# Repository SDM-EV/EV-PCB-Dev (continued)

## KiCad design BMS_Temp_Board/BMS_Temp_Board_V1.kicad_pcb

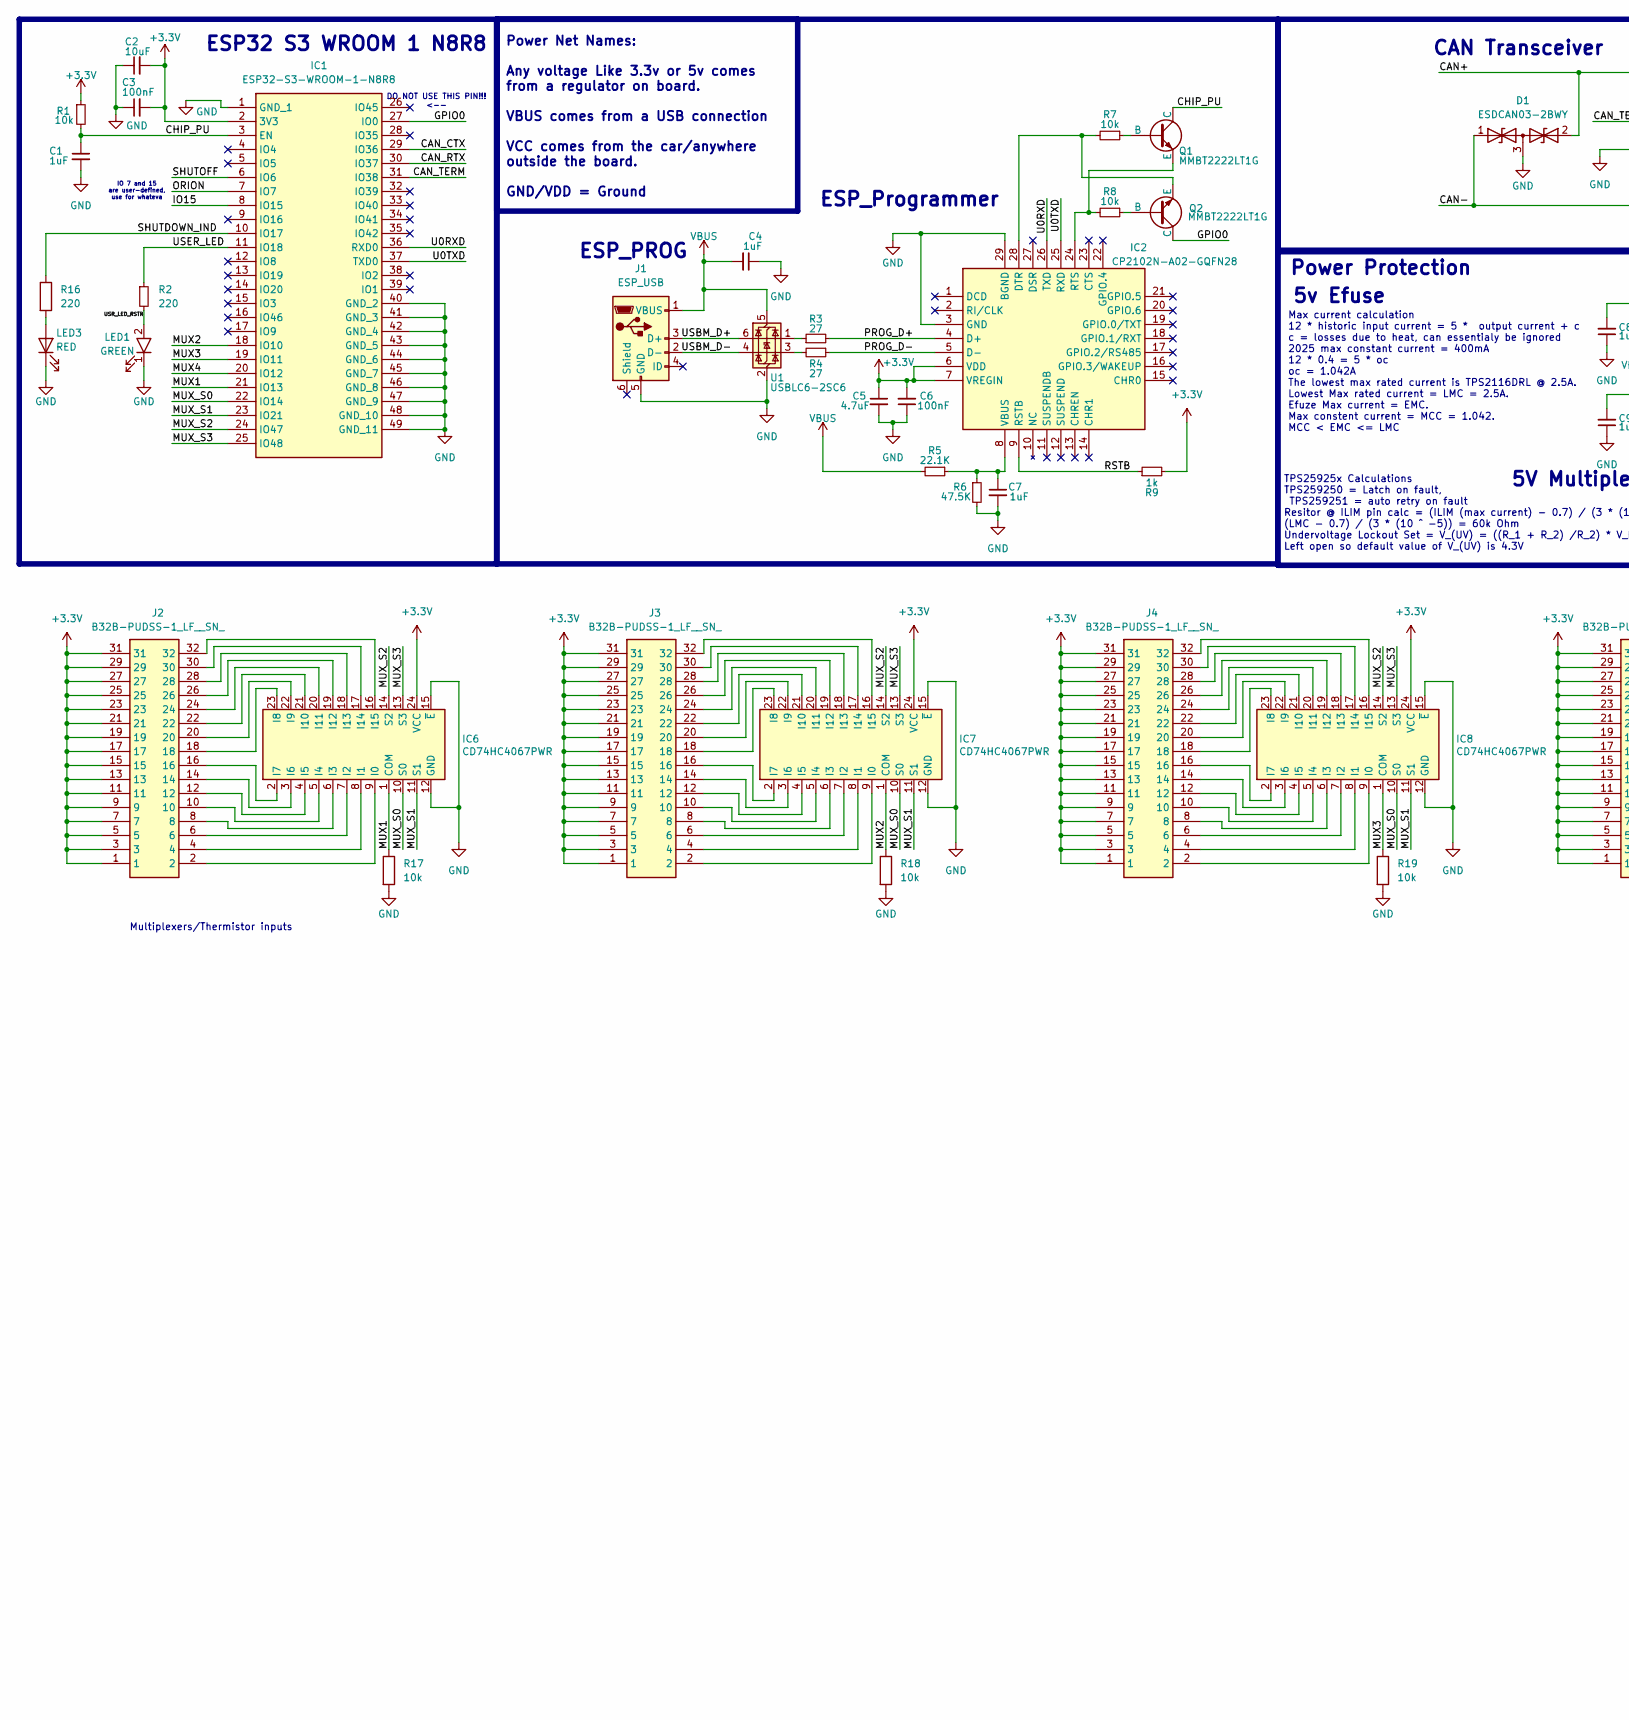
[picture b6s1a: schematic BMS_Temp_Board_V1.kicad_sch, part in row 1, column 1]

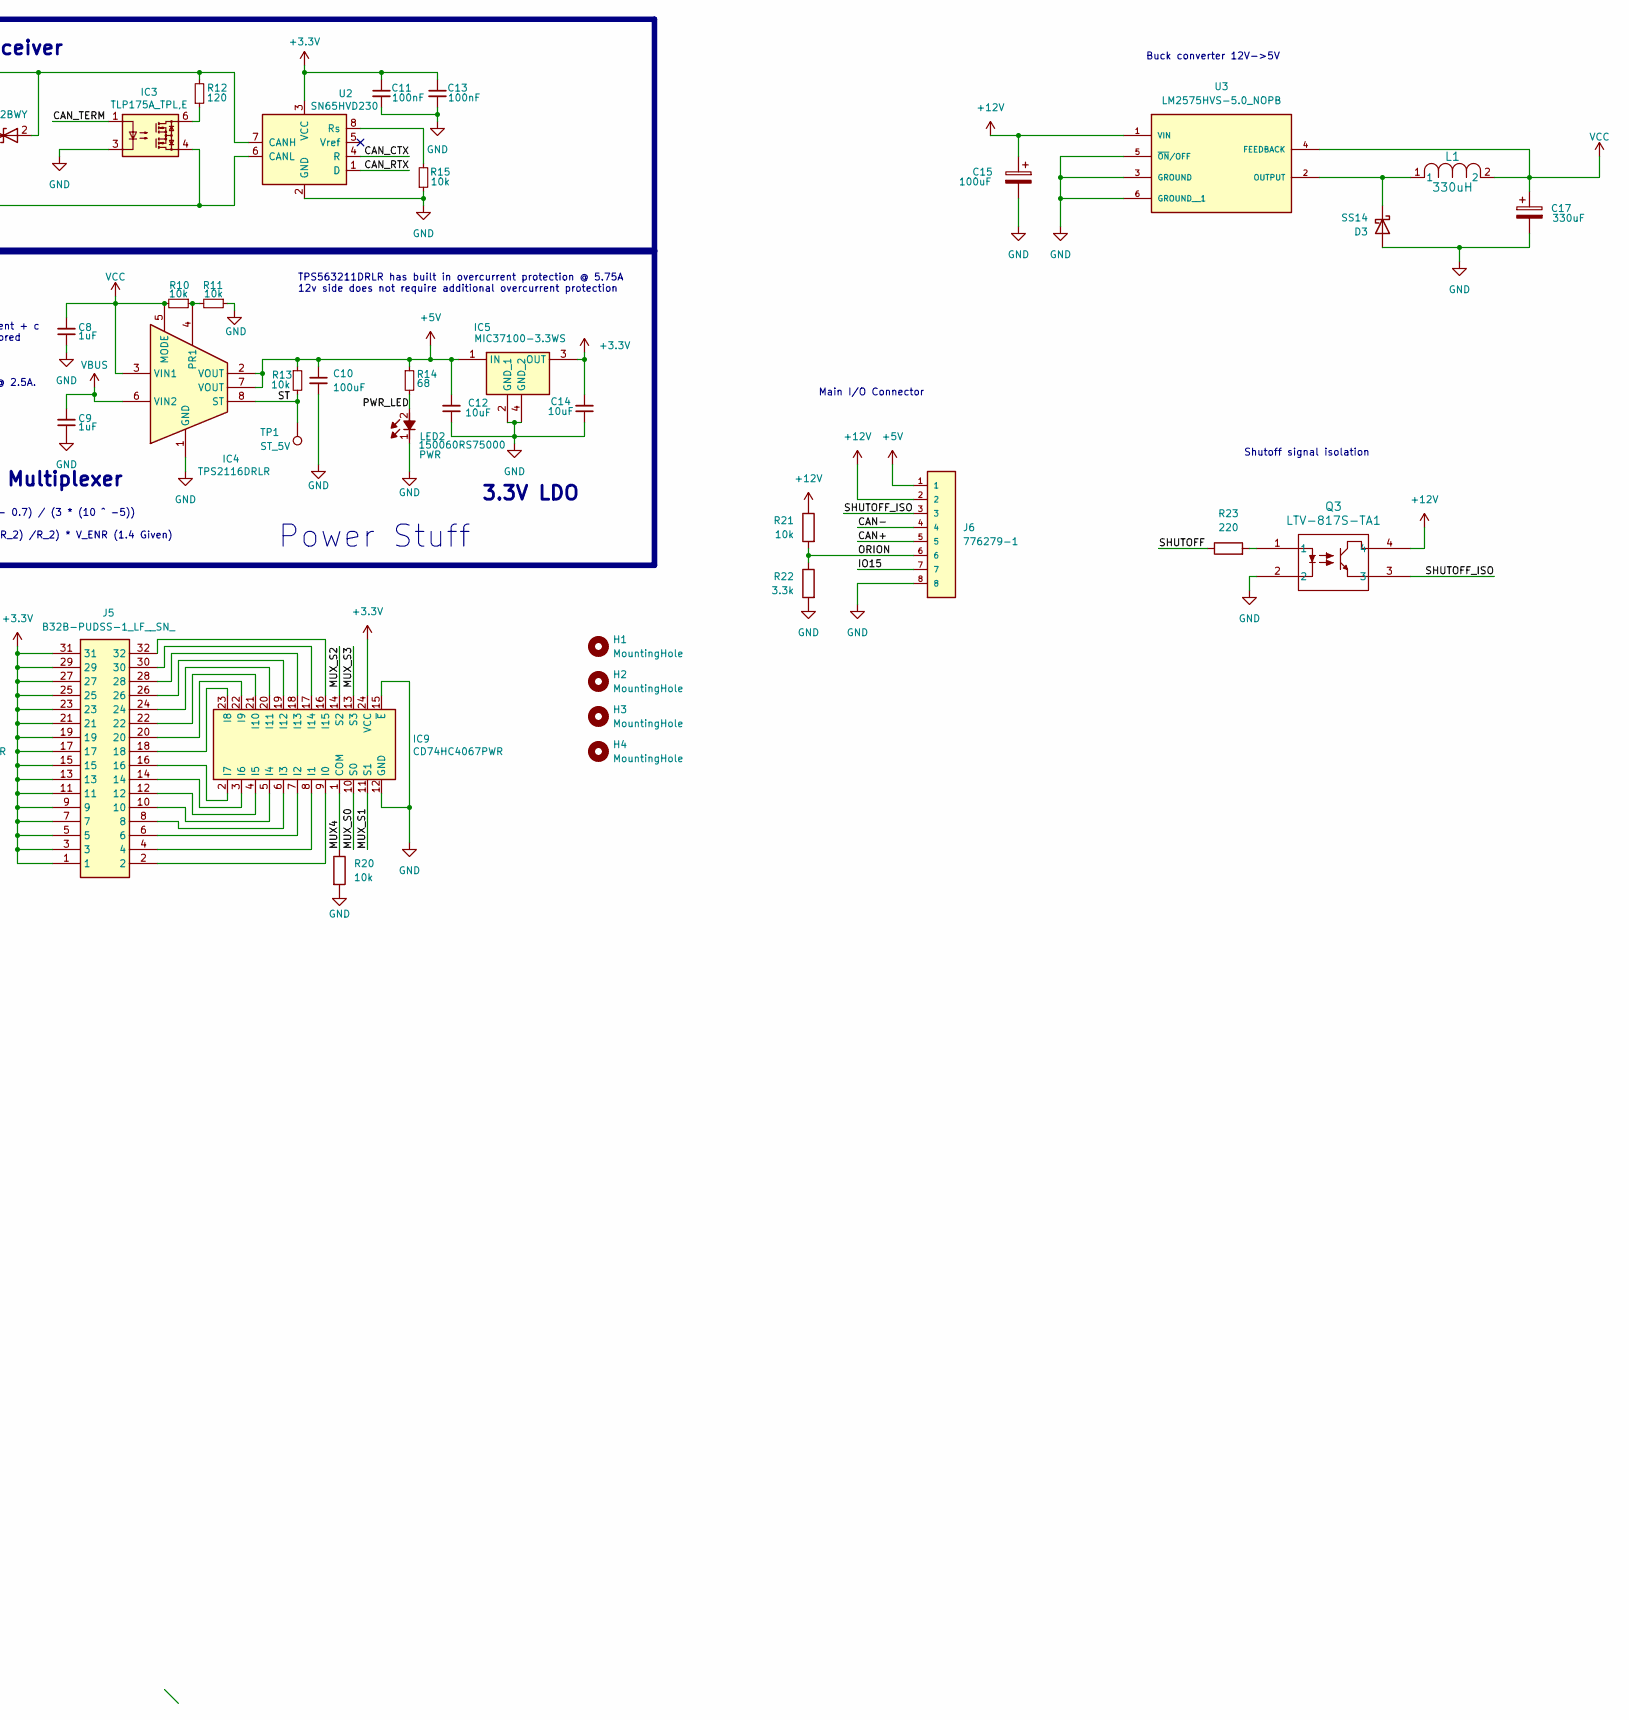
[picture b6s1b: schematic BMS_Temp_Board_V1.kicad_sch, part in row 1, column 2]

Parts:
C1, C4, C7, C8, C9: 1uF; C_0603_1608Metric
C2, C12, C14: 10uF; C_0603_1608Metric
C3, C6, C11, C13: 100nF; C_0603_1608Metric
C5: 4.7uF; C_0603_1608Metric
C10: 100uF; C_1206_3216Metric
C15: 100uF; WCAP-ASLI_6.3X7.7_DXL_
C17: 330uF; CP_Elec_10x10
D1: ESDCAN03-2BWY; SOT-323_SC-70; Mouser Part Number 511-ESDCAN03-2BWY
D3: SS14; D_SMA
H1, H2, H3, H4: MountingHole; MountingHole_2.2mm_M2
IC1: ESP32-S3-WROOM-1-N8R8; XCVR_ESP32S3WROOM1N8R8; Mouser Part Number 356-EP32S3WROOM1N8R8
IC2: CP2102N-A02-GQFN28; QFN50P500X500X80-29N; Mouser Part Number 634-CP2102NA02GQFN28
IC3: TLP175A_TPL,E; 4pin SO6TLP17XX_TOS; Mouser Part Number 757-TLP175A(TPLE
IC4: TPS2116DRLR; SOTFL50P160X60-8N; Mouser Part Number 595-TPS2116DRLR
IC5: MIC37100-3.3WS; SOT-223; Mouser Part Number 998-MIC37100-3.3WS
IC6, IC7, IC8, IC9: CD74HC4067PWR; TSSOP24_4P5X7P9_TEX; Manufacturer_Part_Number CD74HC4067PWR
J1: ESP_USB; USB_Micro-B_Molex-105017-0001
J2, J3, J4, J5: B32B-PUDSS-1_LF__SN_; JST_PUD_B32B-PUDSS_2x16_P2.00mm_Vertical_PN; Mouser Part Number 306-B32BPUDSS1LFSN
J6: 776279-1; TE_776279-1; PARTREV F7
L1: 330uH; IND_SPD127R_API
LED1: GREEN; LED_0603_1608Metric; Mouser Part Number 720-P4112S2U1252X4X5
LED2: 150060RS75000; LED_0603_1608Metric; Mouser Part Number 710-150060RS75000
LED3: RED; LED_0603_1608Metric
Q1, Q2: MMBT2222LT1G; TSOT-23
Q3: LTV-817S-TA1; LTV-817S_LTO
R1, R7, R8, R10, R11, R13, R15, R17, R18, R19, R20, R21: 10k; R_0603_1608Metric
R2, R16, R23: 220; R_0603_1608Metric
R3, R4: 27; R_0603_1608Metric
R5: 22.1K; R_0603_1608Metric
R6: 47.5K; R_0603_1608Metric
R9: 1k; R_0603_1608Metric
R12: 120; R_0603_1608Metric
R14: 68; R_0603_1608Metric
R22: 3.3k; R_0603_1608Metric
TP1: ST_5V; TestPoint_Pad_1.5x1.5mm
U1: USBLC6-2SC6; SOT-23-6
U2: SN65HVD230; SOIC-8_3.9x4.9mm_P1.27mm
U3: LM2575HVS-5.0_NOPB; VREG_LM2575HVS-5.0_NOPB; PARTREV E

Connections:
+3.3V: C2.2, C3.2, C5.1, C6.2, C11.1, C13.1, C14.2, IC1.2 (3V3), IC2.6 (VDD), IC2.7 (VREGIN), IC5.3 (OUT), IC6.24 (VCC), IC7.24 (VCC), IC8.24 (VCC), IC9.24 (VCC), J2.1, J2.3, J2.5, J2.7, J2.9, J2.11, J2.13, J2.15, J2.17, J2.19, J2.21, J2.23, J2.25, J2.27, J2.29, J2.31, J3.1, J3.3, J3.5, J3.7, J3.9, J3.11, J3.13, J3.15, J3.17, J3.19, J3.21, J3.23, J3.25, J3.27, J3.29, J3.31, J4.1, J4.3, J4.5, J4.7, J4.9, J4.11, J4.13, J4.15, J4.17, J4.19, J4.21, J4.23, J4.25, J4.27, J4.29, J4.31, J5.1, J5.3, J5.5, J5.7, J5.9, J5.11, J5.13, J5.15, J5.17, J5.19, J5.21, J5.23, J5.25, J5.27, J5.29, J5.31, R1.1, R9.2, U2.3 (VCC)
+5V: C10.1, C12.2, IC4.2 (VOUT), IC4.7 (VOUT), IC5.1 (IN), J6.1, R13.1, R14.1
+12V: C15.1, J6.2, Q3.4, R21.1, U3.1 (VIN)
/CAN+: D1.2, J6.5, R12.2, U2.7 (CANH)
/CAN-: D1.1, IC3.4, J6.4, U2.6 (CANL)
/CAN_CTX: IC1.29 (IO36), U2.4 (R)
/CAN_RTX: IC1.30 (IO37), U2.1 (D)
/CAN_TERM: IC1.31 (IO38), IC3.1
/CHIP_PU: C1.1, IC1.3 (EN), Q1.3 (C), R1.2
/GPIO0: IC1.27 (IO0), Q2.3 (C)
/IO15: IC1.8 (IO15), J6.7
/MUX1: IC1.21 (IO13), IC6.1 (COM), R17.1
/MUX2: IC1.18 (IO10), IC7.1 (COM), R18.1
/MUX3: IC1.19 (IO11), IC8.1 (COM), R19.1
/MUX4: IC1.20 (IO12), IC9.1 (COM), R20.1
/MUX_S0: IC1.22 (IO14), IC6.10 (S0), IC7.10 (S0), IC8.10 (S0), IC9.10 (S0)
/MUX_S1: IC1.23 (IO21), IC6.11 (S1), IC7.11 (S1), IC8.11 (S1), IC9.11 (S1)
/MUX_S2: IC1.24 (IO47), IC6.14 (S2), IC7.14 (S2), IC8.14 (S2), IC9.14 (S2)
/MUX_S3: IC1.25 (IO48), IC6.13 (S3), IC7.13 (S3), IC8.13 (S3), IC9.13 (S3)
/ORION: IC1.7 (IO7), J6.6, R21.2, R22.1
/PROG_D+: IC2.4 (D+), R3.2
/PROG_D-: IC2.5 (D-), R4.1
/PWR_LED: LED2.2 (A), R14.2
/RSTB: IC2.9 (RSTB), R9.1
/SHUTDOWN_IND: IC1.10 (IO17), R16.1
/SHUTOFF: IC1.6 (IO6), R23.1
/SHUTOFF_ISO: J6.3, Q3.3
/ST: IC4.8 (ST), R13.2, TP1.1
/U0RXD: IC1.36 (RXD0), IC2.26 (TXD)
/U0TXD: IC1.37 (TXD0), IC2.25 (RXD)
/USBM_D+: J1.3 (D+), U1.6 (I/O1)
/USBM_D-: J1.2 (D-), U1.4 (I/O2)
/USER_LED: IC1.11 (IO18), R2.1
/USR_LED_RSTR: LED1.2 (A), R2.2
GND: C1.2, C2.1, C3.1, C4.1, C5.2, C6.1, C7.2, C8.1, C9.1, C10.2, C11.2, C12.1, C13.2, C14.1, C15.2, C17.2, D1.3, D3.2 (A), IC1.1 (GND_1), IC1.40 (GND_2), IC1.41 (GND_3), IC1.42 (GND_4), IC1.43 (GND_5), IC1.44 (GND_6), IC1.45 (GND_7), IC1.46 (GND_8), IC1.47 (GND_9), IC1.48 (GND_10), IC1.49 (GND_11), IC2.3 (GND), IC2.29 (BGND), IC3.3, IC4.1 (GND), IC5.2 (GND_1), IC5.4 (GND_2), IC6.12 (GND), IC6.15 (~E), IC7.12 (GND), IC7.15 (~E), IC8.12 (GND), IC8.15 (~E), IC9.12 (GND), IC9.15 (~E), J1.5 (GND), J6.8, LED1.1 (K), LED2.1 (K), LED3.1 (K), Q3.2, R6.2, R11.1, R15.1, R17.2, R18.2, R19.2, R20.2, R22.2, U1.2 (GND), U2.2 (GND), U3.3 (GROUND), U3.5 (~ON/OFF), U3.6 (GROUND__1)
unnamed: D3.1 (K), L1.1, U3.2 (OUTPUT)
unnamed: IC2.28 (DTR), Q2.2 (E), R7.2
unnamed: IC2.24 (RTS), Q1.2 (E), R8.2
unnamed: C7.1, IC2.8 (VBUS), R5.1, R6.1
unnamed: IC3.6, R12.1
unnamed: IC4.4 (PR1), R10.1, R11.2
unnamed: IC6.9 (I0), J2.2
unnamed: IC6.8 (I1), J2.4
unnamed: IC6.7 (I2), J2.6
unnamed: IC6.6 (I3), J2.8
unnamed: IC6.5 (I4), J2.10
unnamed: IC6.4 (I5), J2.12
unnamed: IC6.3 (I6), J2.14
unnamed: IC6.2 (I7), J2.16
unnamed: IC6.23 (I8), J2.18
unnamed: IC6.22 (I9), J2.20
unnamed: IC6.21 (I10), J2.22
unnamed: IC6.20 (I11), J2.24
unnamed: IC6.19 (I12), J2.26
unnamed: IC6.18 (I13), J2.28
unnamed: IC6.17 (I14), J2.30
unnamed: IC6.16 (I15), J2.32
unnamed: IC7.9 (I0), J3.2
unnamed: IC7.8 (I1), J3.4
unnamed: IC7.7 (I2), J3.6
unnamed: IC7.6 (I3), J3.8
unnamed: IC7.5 (I4), J3.10
unnamed: IC7.4 (I5), J3.12
unnamed: IC7.3 (I6), J3.14
unnamed: IC7.2 (I7), J3.16
unnamed: IC7.23 (I8), J3.18
unnamed: IC7.22 (I9), J3.20
unnamed: IC7.21 (I10), J3.22
unnamed: IC7.20 (I11), J3.24
unnamed: IC7.19 (I12), J3.26
unnamed: IC7.18 (I13), J3.28
unnamed: IC7.17 (I14), J3.30
unnamed: IC7.16 (I15), J3.32
unnamed: IC8.9 (I0), J4.2
unnamed: IC8.8 (I1), J4.4
unnamed: IC8.7 (I2), J4.6
unnamed: IC8.6 (I3), J4.8
unnamed: IC8.5 (I4), J4.10
unnamed: IC8.4 (I5), J4.12
unnamed: IC8.3 (I6), J4.14
unnamed: IC8.2 (I7), J4.16
unnamed: IC8.23 (I8), J4.18
unnamed: IC8.22 (I9), J4.20
unnamed: IC8.21 (I10), J4.22
unnamed: IC8.20 (I11), J4.24
unnamed: IC8.19 (I12), J4.26
unnamed: IC8.18 (I13), J4.28
unnamed: IC8.17 (I14), J4.30
unnamed: IC8.16 (I15), J4.32
unnamed: IC9.9 (I0), J5.2
unnamed: IC9.8 (I1), J5.4
unnamed: IC9.7 (I2), J5.6
unnamed: IC9.6 (I3), J5.8
unnamed: IC9.5 (I4), J5.10
unnamed: IC9.4 (I5), J5.12
unnamed: IC9.3 (I6), J5.14
unnamed: IC9.2 (I7), J5.16
unnamed: IC9.23 (I8), J5.18
unnamed: IC9.22 (I9), J5.20
unnamed: IC9.21 (I10), J5.22
unnamed: IC9.20 (I11), J5.24
unnamed: IC9.19 (I12), J5.26
unnamed: IC9.18 (I13), J5.28
unnamed: IC9.17 (I14), J5.30
unnamed: IC9.16 (I15), J5.32
unnamed: LED3.2 (A), R16.2
unnamed: Q1.1 (B), R7.1
unnamed: Q2.1 (B), R8.1
unnamed: Q3.1, R23.2
unnamed: R3.1, U1.1 (I/O1)
unnamed: R4.2, U1.3 (I/O2)
unnamed: R15.2, U2.8 (Rs)
VBUS: C4.2, C9.2, IC4.6 (VIN2), J1.1 (VBUS), R5.2, U1.5 (VBUS)
VCC: C8.2, C17.1, IC4.3 (VIN1), IC4.5 (MODE), L1.2, R10.2, U3.4 (FEEDBACK)

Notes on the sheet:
Buck converter 12V->5V
Power Protection
Power Stuff
Shutoff signal isolation
IO 7 and 15 are user-defined, use for whateva
Multiplexers/Thermistor inputs
3.3V LDO
TPS563211DRLR has built in overcurrent protection @ 5.75A 12v side does not require additional overcurrent protection
5v Efuse
TPS25925x Calculations TPS259250 = Latch on fault, TPS259251 = auto retry on fault Resitor @ ILIM pin calc = (ILIM (max current) - 0.7) / (3 * (10 ^ -5)) (LMC - 0.7) / (3 * (10 ^ -5)) = 60k Ohm Undervoltage Lockout Set = V_(UV) = ((R_1 + R_2) /R_2) * V_ENR (1.4 Given) Left open so default value of 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
ESP_PROG
CAN Transceiver
5V Multiplexer
DO NOT USE THIS PIN!!! <--
Main I/O Connector
Max current calculation 12 * historic input current = 5 * output current + c c = losses due to heat, can essentialy be ignored 2025 max constant current = 400mA 12 * 0.4 = 5 * oc oc = 1.042A The lowest max rated current is TPS2116DRL @ 2.5A. Lowest Max rated current = LMC = 2.5A. Efuze Max current 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
ESP32 S3 WROOM 1 N8R8
ESP_Programmer
Power Net Names: Any voltage Like 3.3v or 5v comes from a regulator on board. VBUS comes from a USB connection VCC comes from the car/anywhere outside the board. GND/VDD = Ground

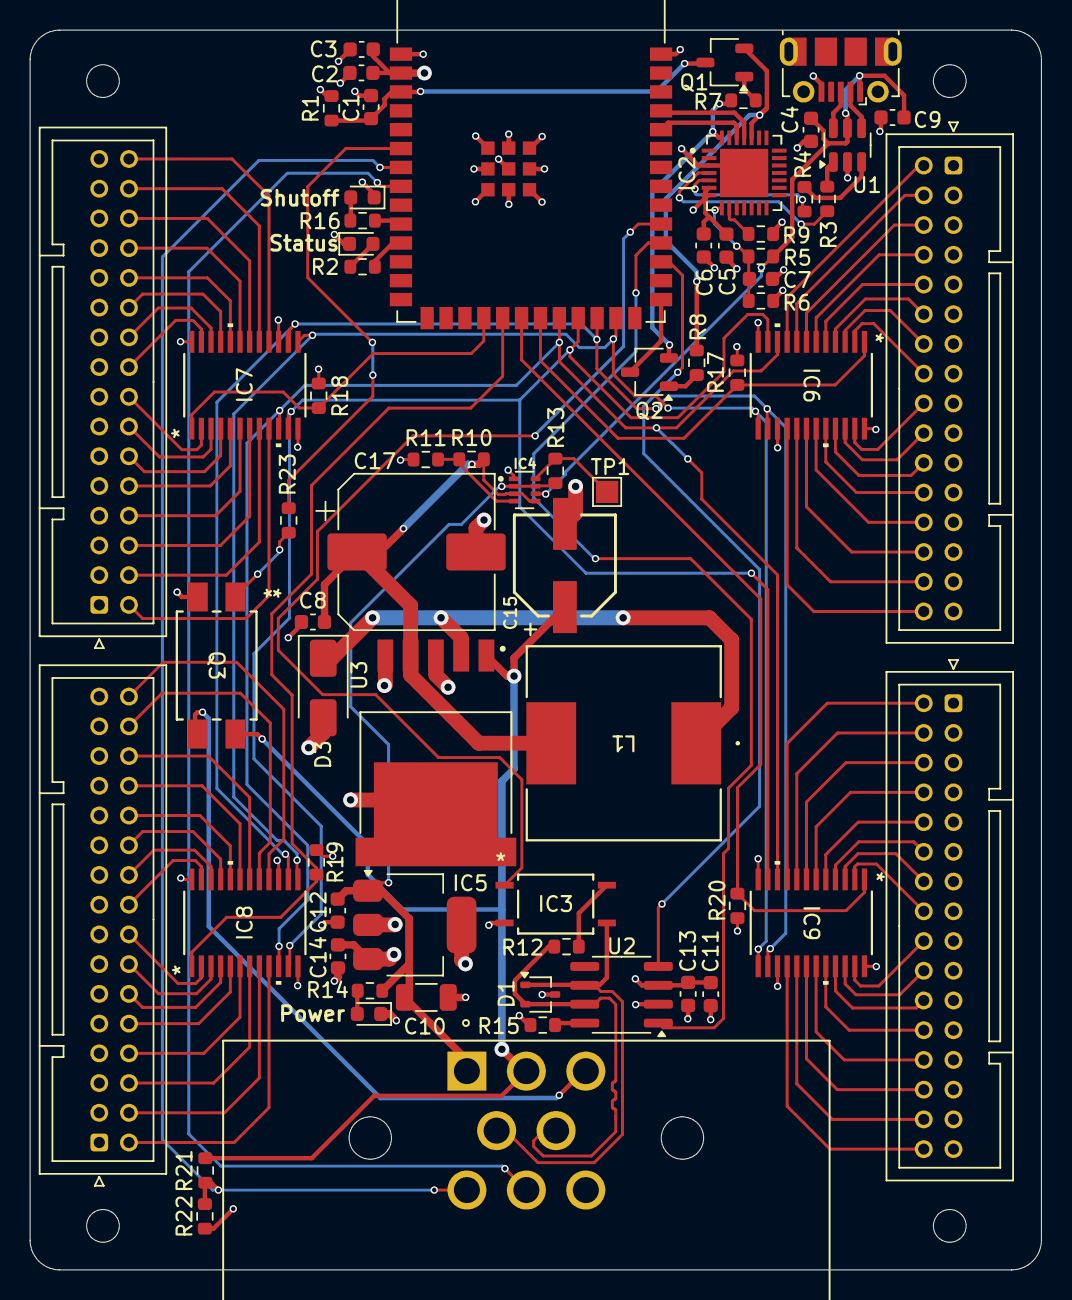
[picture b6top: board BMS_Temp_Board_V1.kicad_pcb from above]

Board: 4 copper layers, 68.0 x 83.4 mm, 71 parts (0 on the bottom side), 114 nets.

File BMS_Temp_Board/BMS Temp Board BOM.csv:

"Reference","Qty","Value","DNP","Exclude from BOM","Exclude from Board","Footprint","Datasheet"
"C1,C4,C7,C8,C9","5","1uF","","","","Capacitor_SMD:C_0603_1608Metric","~"
"C2,C12,C14","3","10uF","","","","Capacitor_SMD:C_0603_1608Metric","~"
"C3,C6,C11,C13","4","100nF","","","","Capacitor_SMD:C_0603_1608Metric","~"
"C5","1","4.7uF","","","","Capacitor_SMD:C_0603_1608Metric","~"
"C10","1","100uF","","","","Capacitor_SMD:C_1206_3216Metric","~"
"C15","1","100uF","","","","865080545012:WCAP-ASLI_6.3X7.7_DXL_","~"
"C17","1","330uF","","","","Capacitor_SMD:CP_Elec_10x10","~"
"D1","1","ESDCAN03-2BWY","","","","Package_TO_SOT_SMD:SOT-323_SC-70","https://www.mouser.de/datasheet/2/389/esdcan02-2bwy-954689.pdf"
"D3","1","SS14","","","","Diode_SMD:D_SMA","http://www.vishay.com/docs/88525/1n5817.pdf"
"H1,H2,H3,H4","4","MountingHole","","Excluded from BOM","","MountingHole:MountingHole_2.2mm_M2","~"
"IC1","1","ESP32-S3-WROOM-1-N8R8","","","","ESP32_S3_WROOM_1_N8R8:XCVR_ESP32S3WROOM1N8R8","https://www.espressif.com/sites/default/files/documentation/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"
"IC2","1","CP2102N-A02-GQFN28","","","","CP2102N_A02_GQFN28:QFN50P500X500X80-29N","https://componentsearchengine.com/Datasheets/2/CP2102N-A02-G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"
"IC3","1","TLP175A_TPL,E","","","","TPL175A:4pin SO6TLP17XX_TOS","http://toshiba.semicon-storage.com/info/docget.jsp?did=13665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"
"IC4","1","TPS2116DRLR","","","","TPS2116DRLR:SOTFL50P160X60-8N","https://www.ti.com/lit/gpn/tps2116"
"IC5","1","MIC37100-3.3WS","","","","Package_TO_SOT_SMD:SOT-223","https://datasheet.datasheetarchive.com/originals/dk/DKDS-15/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"
"IC6,IC7,IC8,IC9","4","CD74HC4067PWR","","","","CD74HC4067PWR:TSSOP24_4P5X7P9_TEX","https://www.ti.com/lit/ds/symlink/cd74hc4067.pdf?ts=1752945808096"
"J1","1","ESP_USB","","","","Connector_USB:USB_Micro-B_Molex-105017-0001","~"
"J2,J3,J4,J5","4","B32B-PUDSS-1_LF__SN_","","","","ESP32_S3_WROOM_1_N8R8:JST_PUD_B32B-PUDSS_2x16_P2.00mm_Vertical_PN","https://www.jst-mfg.com/product/pdf/eng/ePUD.pdf"
"J6","1","776279-1","","","","776279_1:TE_776279-1",""
"L1","1","330uH","","","","Nadine:IND_SPD127R_API","SPD127R-334M"
"LED1","1","GREEN","","","","LED_SMD:LED_0603_1608Metric",""
"LED2","1","150060RS75000","","","","LED_SMD:LED_0603_1608Metric","https://www.we-online.com/components/products/datasheet/1500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"
"LED3","1","RED","","","","LED_SMD:LED_0603_1608Metric","~"
"Q1,Q2","2","MMBT2222LT1G","","","","Package_TO_SOT_SMD:TSOT-23","https://ngspice.sourceforge.io/docs/ngspice-html-manual/manu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"
"Q3","1","LTV-817S-TA1","","","","LTV_817S_TA1:LTV-817S_LTO","LTV-817S-TA1"
"R1,R7,R8,R10,R11,R13,R15,R17,R18,R19,R20,R21","12","10k","","","","Resistor_SMD:R_0603_1608Metric","~"
"R2,R16,R23","3","220","","","","Resistor_SMD:R_0603_1608Metric","~"
"R3,R4","2","27","","","","Resistor_SMD:R_0603_1608Metric","~"
"R5","1","22.1K","","","","Resistor_SMD:R_0603_1608Metric","~"
"R6","1","47.5K","","","","Resistor_SMD:R_0603_1608Metric","~"
"R9","1","1k","","","","Resistor_SMD:R_0603_1608Metric","~"
"R12","1","120","","","","Resistor_SMD:R_0603_1608Metric","~"
"R14","1","68","","","","Resistor_SMD:R_0603_1608Metric","~"
"R22","1","3.3k","","","","Resistor_SMD:R_0603_1608Metric","~"
"TP1","1","ST_5V","","","","TestPoint:TestPoint_Pad_1.5x1.5mm","~"
"U1","1","USBLC6-2SC6","","","","Package_TO_SOT_SMD:SOT-23-6","https://www.st.com/resource/en/datasheet/usblc6-2.pdf"
"U2","1","SN65HVD230","","","","Package_SO:SOIC-8_3.9x4.9mm_P1.27mm","http://www.ti.com/lit/ds/symlink/sn65hvd230.pdf"
"U3","1","LM2575HVS-5.0_NOPB","","","","Nadine:VREG_LM2575HVS-5.0_NOPB","https://mm.digikey.com/Volume0/opasdata/d220001/medias/docus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"

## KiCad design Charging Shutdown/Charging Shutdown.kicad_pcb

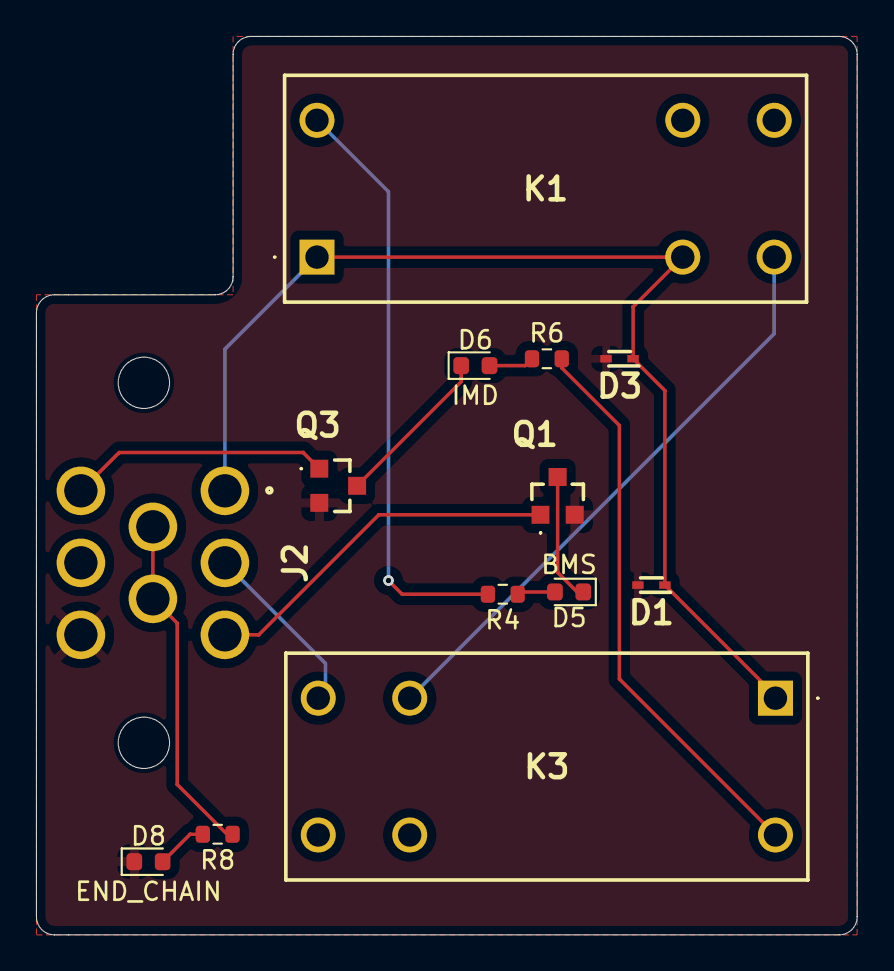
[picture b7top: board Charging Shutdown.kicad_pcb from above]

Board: 2 copper layers, 45.6 x 49.9 mm, 13 parts (0 on the bottom side), 14 nets.

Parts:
D1, D3: D; SODFL1608X70N
D5: BMS; LED_0603_1608Metric
D6: IMD; LED_0603_1608Metric
D8: END_CHAIN; LED_0603_1608Metric
J2: 776280-1
K1, K3: PR2212V4001A
Q1, Q3: 2N2222; ZXM61N02FTC
R4, R6, R8: 220; R_0603_1608Metric

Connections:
+12V: D1.1 (K), D3.1 (K), J2.1, K1.1 (COIL_1), K1.2 (COM_1), K3.1 (COIL_1)
/BMS KILL SIGNAL: J2.3, Q1.1 (G)
/IMD KILL SIGNAL: J2.6, Q3.1 (G)
/RELAYS_OUT: J2.2, K3.3 (NO_1)
GND: D1.2 (A), D3.2 (A), D8.1 (K), J2.8, Q1.3 (S), Q3.3 (S)
unnamed: D5.2 (A), R4.1
unnamed: D5.1 (K), Q1.2 (D)
unnamed: D6.2 (A), R6.1
unnamed: D6.1 (K), Q3.2 (D)
unnamed: D8.2 (A), R8.2
unnamed: K1.6 (COIL_2), R4.2
unnamed: K1.3 (NO_1), K3.2 (COM_1)
unnamed: K3.6 (COIL_2), R6.2
Shutdown Signal: J2.4, J2.5, R8.1

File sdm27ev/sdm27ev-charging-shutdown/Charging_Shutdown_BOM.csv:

"Reference","Qty","Value","DNP","Exclude from BOM","Exclude from Board","Footprint","Datasheet"
"D1,D3","2","D","","","","Diode_SMD:SODFL1608X70N","~"
"D5","1","BMS","","","","LED_SMD:LED_0201_0603Metric","~"
"D6","1","IMD","","","","LED_SMD:LED_0201_0603Metric","~"
"D8","1","END_CHAIN","","","","LED_SMD:LED_0201_0603Metric","~"
"J2","1","776280-1","","","","SDM_MiscFootprint:776280-1","https://www.te.com/commerce/DocumentDelivery/DDEController?A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"
"K1,K3","2","PR2212V4001A","","","","Shutdown_Footprint:PR2212V4001A","https://www.sameskydevices.com/product/resource/PR22-12V-400-1A.pdf"
"Q1,Q3","2","2N2222","","","","Shutdown_Footprint:ZXM61N02FTC","https://www.diodes.com/assets/Datasheets/ZXM61N02F.pdf"
"R4,R6,R8","3","220","","","","Resistor_SMD:R_0201_0603Metric","~"

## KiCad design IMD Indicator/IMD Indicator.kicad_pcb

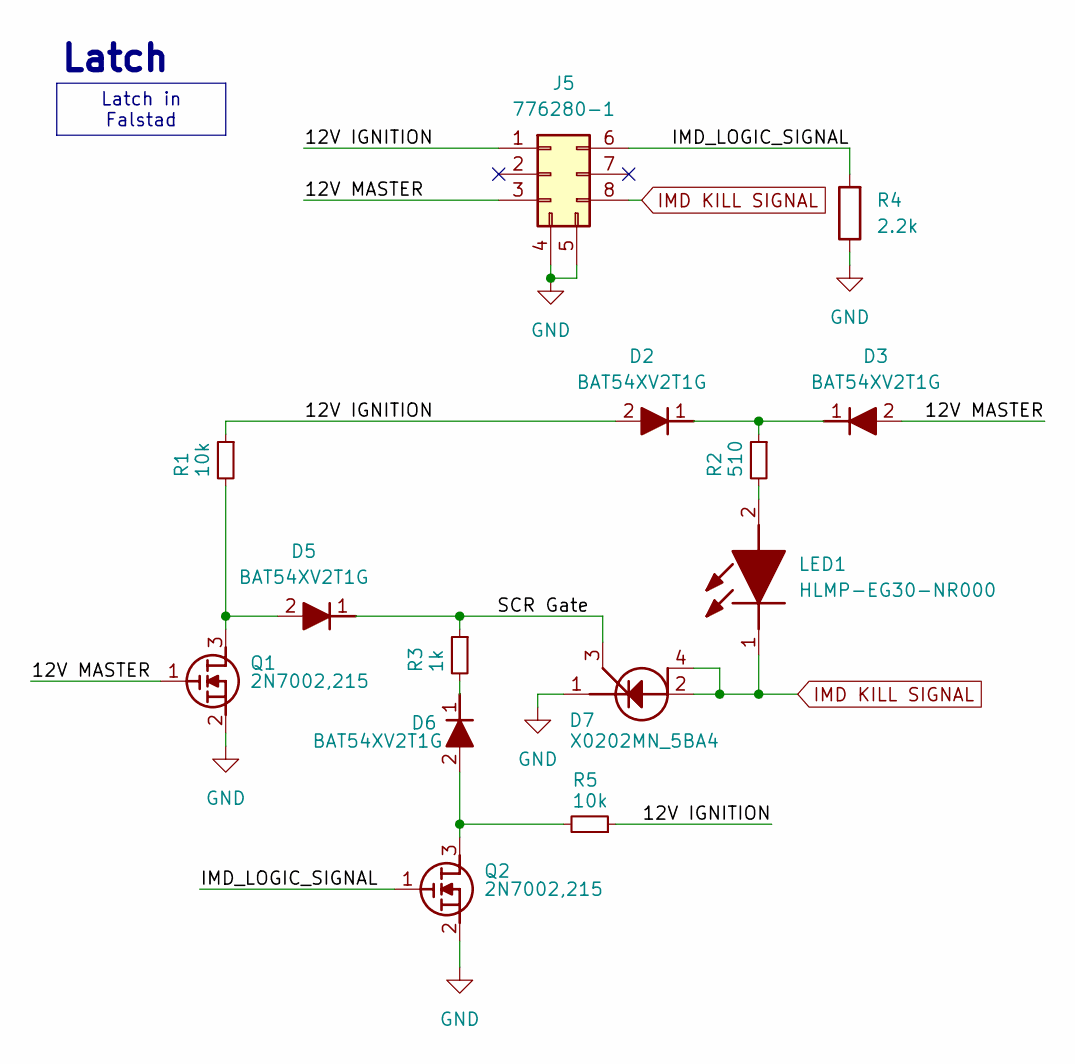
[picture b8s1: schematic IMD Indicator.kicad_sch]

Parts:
D2, D3, D5, D6: BAT54XV2T1G; SODFL1608X70N; Mouser Part Number 863-BAT54XV2T1G
D7: X0202MN_5BA4; SOT230P700X190-4N; Mouser Part Number 511-X0202MN
J5: 776280-1; Mouser Part Number 571-776280-1
LED1: HLMP-EG30-NR000; LED_5MM; Mouser Part Number 630-HLMP-EG30-NR000
Q1, Q2: 2N7002,215; SOT95P230X110-3N; Mouser Part Number 771-2N7002-T/R
R1, R5: 10k; R_0603_1608Metric
R2: 510; R_0603_1608Metric
R3: 1k; R_0603_1608Metric
R4: 2.2k; R_0603_1608Metric

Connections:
/12V IGNITION: D2.2 (A), J5.1, R1.1, R5.1
/12V MASTER: D3.2 (A), J5.3, Q1.1 (G)
/IMD_LOGIC_SIGNAL: J5.6, Q2.1 (G), R4.2
/SCR Gate: D5.1 (K), D7.3 (G), R3.1
GND: D7.1 (K), J5.4, J5.5, Q1.2 (S), Q2.2 (S), R4.1
IMD KILL SIGNAL: D7.2 (A_1), D7.4 (A_2), J5.8, LED1.1 (K)
unnamed: D2.1 (K), D3.1 (K), R2.1
unnamed: D5.2 (A), Q1.3 (D), R1.2
unnamed: D6.2 (A), Q2.3 (D), R5.2
unnamed: D6.1 (K), R3.2
unnamed: LED1.2 (A), R2.2

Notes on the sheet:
Latch
Latch in Falstad

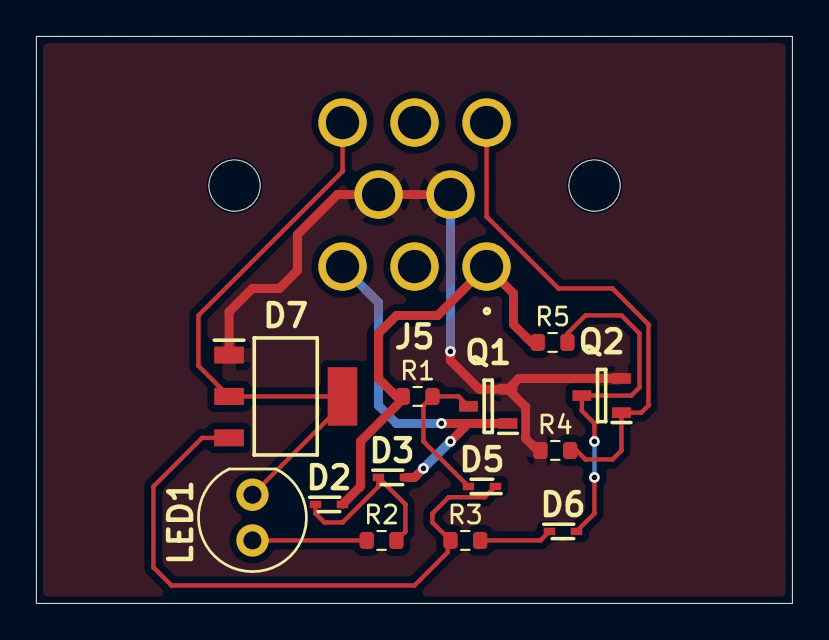
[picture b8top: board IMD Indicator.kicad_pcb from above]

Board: 2 copper layers, 42.0 x 31.5 mm, 14 parts (0 on the bottom side), 11 nets.

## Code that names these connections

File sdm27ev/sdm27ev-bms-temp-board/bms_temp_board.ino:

const int mux1 = 13, mux2 = 10, // define mux input pins
          mux3 = 11, mux4 = 12; // we have 4 muxes

const int mux_s0 = 14, mux_s1 = 21, // define mux address pins
          mux_s2 = 47, mux_s3 = 48; // each mux has 16 (2^4) inputs

const int shutoff = 6, shutoff_led = 17, user_led = 18; // define shutoff and custom led outputs

const float max_temp = 60.0; // shutdown temperature in deg. C, should be 60 or less

const float init_temp = 25.0; // initial temperature to maintain accuracy in first few cycles

const float A = 1.3512 * pow(10,-3), B = 8.1227 * pow(10,-5), // coefficients for thermistor curve
            C = 2.0801 * pow(10,-5), D = -6.5251 * pow(10,-7); // Steinhart-Hart equation

const int samples = 5; // how many samples we want to store/average

int mux_inputs[4] = {mux1, mux2, mux3, mux4}; // mux pins

float temp_record[64][samples] = {{init_temp},{init_temp}}; // last recorded temp values

float temp_averages[64] = {init_temp};

float adc_to_temp (int adc_in) { // convert ADC reading (0-4095) to celsius
  float therm_R = (adc_in/4096.0) * 10000; // thermistor resistance, 10k is fixed resistor
  float ln_therm_R = log(therm_R); // calculate natural log once to save time
  // Steinhart-Hart equation to calculate temperature in celsius
  float therm_T = 1 / (A + B*ln_therm_R + C*pow(ln_therm_R,2) + D*pow(ln_therm_R,3)) + 273.15;
  return therm_T;
}

void shift_temps(float temp_record[64][samples]) { // shifts samples right to make space for new value
  for (int i = 0; i < 64; i++) {
    for (int j = samples; j > 0; j--) {
      temp_record[i][j] = temp_record[i][j-1];
    }
  }
}



void shutdown() { // write shutoff signal/led high and wait until reset
  digitalWrite(shutoff, HIGH);
  digitalWrite(shutoff_led, HIGH);
  exit(0);
}

void setup() {
  // set pinmodes
  pinMode(mux1, INPUT); pinMode(mux2, INPUT); pinMode(mux3, INPUT); pinMode(mux4, INPUT);
  pinMode(mux_s0, OUTPUT); pinMode(mux_s1, OUTPUT); pinMode(mux_s2, OUTPUT); pinMode(mux_s3, OUTPUT);
}

void loop() {
  // temperature data collection:
  for (int count = 0; count < 16; count++) { // count up binary address 0 to 15
    shift_temps(temp_record); // shift to make room for new data

    digitalWrite(mux_s0, count & 0b0001); // output binary address to each address pin
    digitalWrite(mux_s1, count & 0b0010); // & is bitwise AND
    digitalWrite(mux_s2, count & 0b0100);
    digitalWrite(mux_s3, count & 0b1000);

    for (int i = 0; i < 4; i++) { // convert to temperature and record samples
      temp_record[count*i][0] = adc_to_temp(analogRead(mux_inputs[i]));
    }

    // average samples
    for (int i = 0; i < 64; i++) {
      float temp_row_sum = 0; // initialize sum to 0
      for (int j = 0; j < samples; j++) {
        temp_row_sum += temp_record[i][j]; // add together all samples from one thermistor
      }
      temp_averages[i] = temp_row_sum / samples; // average samples and write to array
    }
  }

  // check for shutdown criteria on each temperature
  for (int i = 0; i < 64; i++) {
    if (temp_averages[i] >= max_temp) {
      shutdown();
    }
  }
}

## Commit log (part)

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2025-10-10 setting up ur shit
2025-10-25 EV BSPD project
2025-10-25 Motor Controller
2025-10-31 BSE temp stuff
2025-10-31 BMS_Temp
    added mux
2025-11-01 12v Circuit added
2025-11-01 12v controller
2025-11-21 BSPD PCB
2025-11-26 ESP32S3 MCU template
2025-11-26 ESP32 MCU update
2025-12-05 Global Libraries Added
2025-12-06 Library Update
2025-12-06 Temp Board
2025-12-09 fixes
    reset template properly, redid board, and fixed libraries
2025-12-24 started pcb design
2026-01-17 pcb progress
2026-01-18 Voltage Indicator PCB
2026-01-18 Revert "Voltage Indicator PCB"
    This reverts commit c1b8267dc4e6873464caab4cd078e1dd8b23caf2.
2026-01-23 Revert "TSSI Kicad Schematic.kicad_sch"
2026-01-23 initial TSSI Arduino Code
    simple setup & loop
2026-01-24 Therm temp board 2
2026-02-06 Temp board PCB design
2026-02-08 Revised BMS Temperature Board and precharge circuit
    the precharge circuit is a *very* basic schematic, not really finished
2026-02-21 (hopefully) final revision of the bms temp board
2026-02-21 12 volt PCB
2026-02-21 Voltage Indicator All Files
2026-02-25 updating bms temp board
2026-02-28 Shutdown Circuit Design
2026-03-06 Discharge Circuit PCB
2026-03-18 Discharge circuit done for matt s
2026-03-22 Reviewing Board
    Ready for DAQ Review
2026-03-25 Cleaning the BMS Folder
2026-03-25 BSPD V1.2, Shutdown Circuit, Charging Shutdown Circuit, Voltage Indicator
2026-03-25 Ready_to_Move_Lights
    Ready to Move Lights kicad files
2026-03-25 IMD Indicator
2026-03-26 12 v power supply pcb with mounting holes
2026-03-28 changed C17 and some layout on bms temp
2026-03-28 Fully Updated 12 V PCB with correct Gerber Files
2026-03-28 made changes from design review
2026-03-28 changed capacitor footprint, prolly something else too
2026-03-29 BSPD, Shutdown/Charging Shutdown, & Voltage Indicator final changes
2026-03-29 Voltage Indicator Fixed fr fr
2026-03-29 Voltage Indicator with comparator :(
2026-03-29 Fixed some silkscreen labels
2026-03-29 Fixed a net in BSPD and added isolated 5V line in voltage indicator
2026-03-29 fixed reset button and connect logic signal to SCR gate
2026-03-30 updated datasheets, part numbers, and price/stock
2026-03-30 Ready_to_Move_Lights
    Updated ready to move lights schematic and pcb
2026-03-30 Fixed Ready_to_Move_Lights
    Noticed this morning i didnt pay attention and messed up the connector placement
2026-04-01 changed LED (symbol, footprint)
2026-04-10 Ready to Move Lights
    Added some cad models for easier visual
2026-04-13 Added larger components to 3d models
2026-04-13 Moved relay position
2026-04-13 Added models to fixed charging shutdown
2026-04-15 Changes
    all good
2026-04-18 Redesigned BMS Temp Board for 64 thermistors
2026-04-18 Fixed Voltage Indicator Board Shape
2026-04-18 Old stuff
2026-04-20 TSSI Schematic Update to Main
    After this, we can delete the TSSI branch as it is too far behind and does not contain any files necessary for the main.
2026-04-20 Ready_to_Move_Lights Changes
    Fixed accidental wiring on 555 output, changed lights' resistors, compressed whole PCB, improved decoupling cap placement
2026-04-23 lights n stuff
2026-04-24 removed unnecessary connectors from sch & layout, added pulldown resistor
2026-04-25 Cleaning files
2026-04-25 removed extra connectors from sch & layout
2026-04-25 Changed temp board to use ampseal connector
2026-05-02 Added Orion input to temp board
2026-05-02 New relay, added holes
2026-05-02 Added flyback diode
2026-06-01 MC 12V BOM
2026-06-27 Footprint fixes for Charging Shutdown + Gerbers
2026-06-28 Added optoisolator to shutoff signal output, updated BOM
